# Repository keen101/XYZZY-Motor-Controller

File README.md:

# XYZZY-Motor-Controller
Open Source Hardware XYZZY Motor Controller Prototype
By Andrew Barney
Loveland, Colorado, USA
Nov-24-17

umm.. So this is a github of the XYZZY Open Source Motor Controller. It is currently not completley functional or ironed out. 80% complete. Needs some TLC.

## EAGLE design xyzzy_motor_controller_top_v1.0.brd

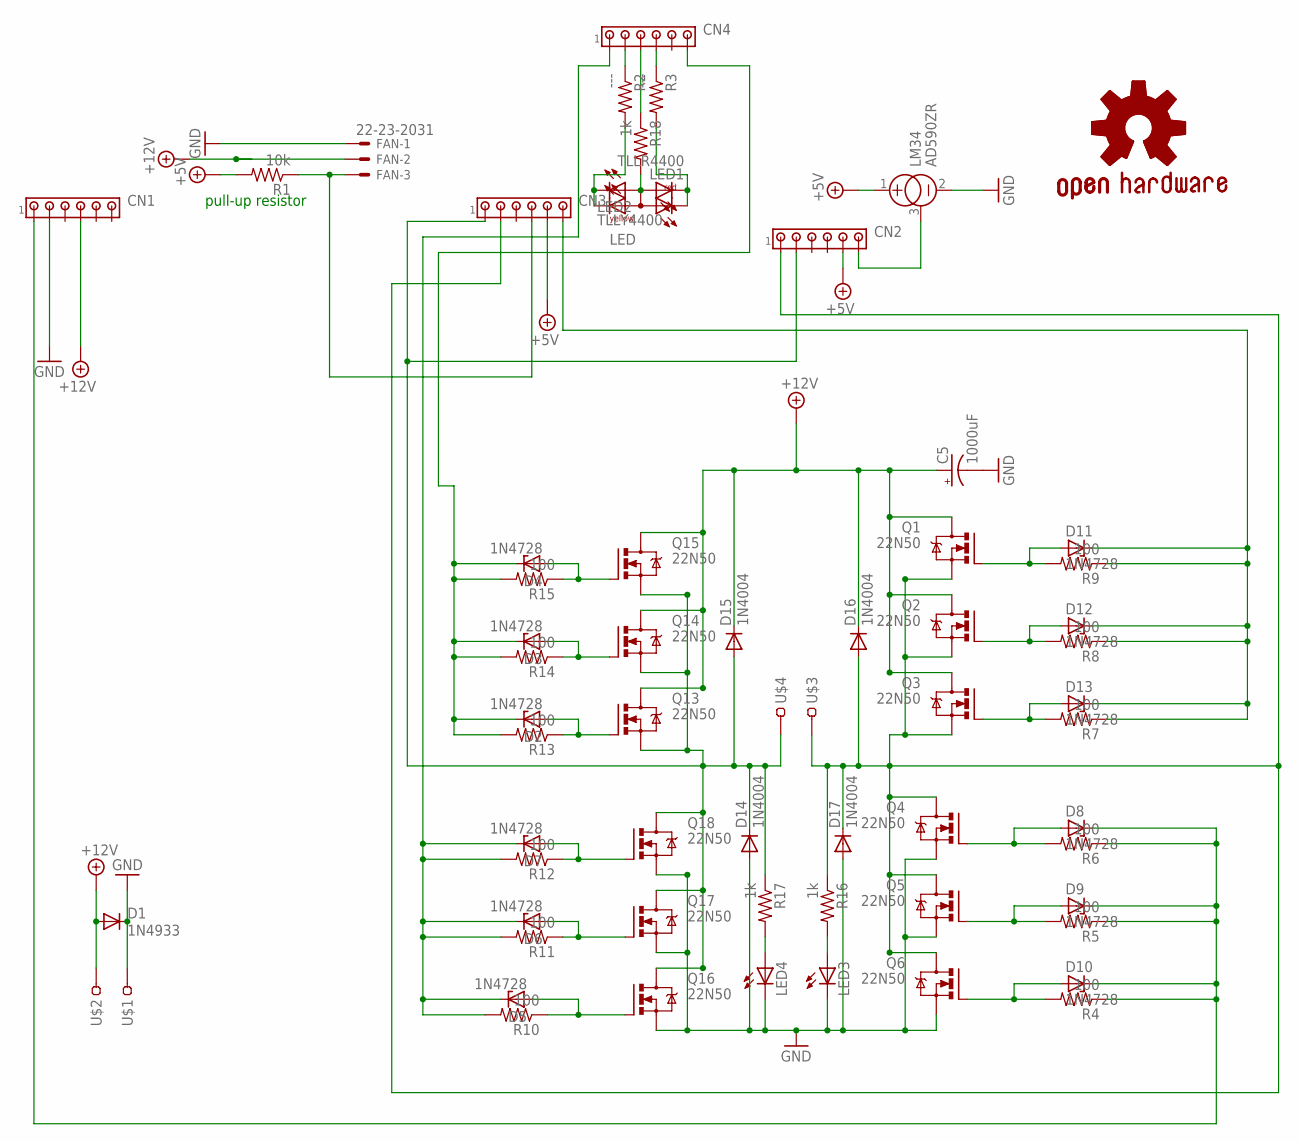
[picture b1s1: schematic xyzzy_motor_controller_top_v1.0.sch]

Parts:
C5: 1000uF; E5-13
CN1, CN2, CN3, CN4: MTA06-100; 10X06MTA
D1: 1N4933; DO41-10
D2, D3, D4, D5, D6, D7, D8, D9, D10, D11, D12, D13: 1N4728; DO41Z10
D14, D15, D16, D17: 1N4004; DO41-10
FAN: 22-23-2031
GOLD_ORB_SM2: OSHWLOGO_GOLD_ORB_MED; OSHW1
LED: DUOLED-RY-A; DUOLED-A-5MM
LED1: TLLR4400; LED3MM
LED2: TLLY4400; LED3MM
LED3, LED4: LED3MM
LM34: AD590ZR; TO92
Q1, Q2, Q3, Q4, Q5, Q6, Q13, Q14, Q15, Q16, Q17, Q18: 22N50; TO220BV
R1: 10k; 0207/12
R2, R3: ---; 0207/12
R4, R5, R6, R7, R8, R9, R10, R11, R12, R13, R14, R15: 100; 0207/12
R16, R17, R18: 1k; 0207/12
U$1, U$2, U$3, U$4: TAB-CON; SPADE

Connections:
+5V: CN2.5, CN3.5, LM34.1 (+), R1.2
+12V: C5.+, CN1.4, D1.A, D15.C, D16.C, FAN.2, Q1.D, Q2.D, Q3.D, Q13.D, Q14.D, Q15.D, U$2.P$1, U$2.P$2
GND: C5.-, CN1.2, D1.C, D14.A, D17.A, FAN.1, LED3.K (C), LED4.K (C), LM34.2 (-), Q4.S, Q5.S, Q6.S, Q16.S, Q17.S, Q18.S, U$1.P$1, U$1.P$2
unnamed: CN3.4, FAN.3, R1.1
unnamed: CN2.6, LM34.3 (CAN)
unnamed: CN2.2, CN3.1, D14.C, D15.A, Q13.S, Q14.S, Q15.S, Q16.D, Q17.D, Q18.D, R17.1, U$4.P$1, U$4.P$2
unnamed: D8.A, Q4.G, R6.2
unnamed: LED.CX (CY), LED2.K (C), R2.2
unnamed: CN4.2, R2.1
unnamed: CN4.1, D5.C, D6.C, D7.C, R10.2, R11.2, R12.2
unnamed: CN3.6, D11.C, D12.C, D13.C, R7.1, R8.1, R9.1
unnamed: CN4.4, R3.1
unnamed: LED.CR, LED1.K (C), R3.2
unnamed: LED3.A, R16.2
unnamed: D10.A, Q6.G, R4.2
unnamed: D9.A, Q5.G, R5.2
unnamed: D7.A, Q18.G, R12.1
unnamed: CN4.6, D2.C, D3.C, D4.C, R13.2, R14.2, R15.2
unnamed: CN1.1, D8.C, D9.C, D10.C, R4.1, R5.1, R6.1
unnamed: LED4.A, R17.2
unnamed: D6.A, Q17.G, R11.1
unnamed: CN2.1, CN3.2, D16.A, D17.C, Q1.S, Q2.S, Q3.S, Q4.D, Q5.D, Q6.D, R16.1, U$3.P$1, U$3.P$2
unnamed: D5.A, Q16.G, R10.1
unnamed: CN4.3, R18.1
unnamed: LED.A, LED1.A, LED2.A, R18.2
unnamed: D12.A, Q2.G, R8.2
unnamed: D11.A, Q1.G, R9.2
unnamed: D13.A, Q3.G, R7.2
unnamed: D3.A, Q14.G, R14.1
unnamed: D4.A, Q15.G, R15.1
unnamed: D2.A, Q13.G, R13.1

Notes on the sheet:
pull-up resistor

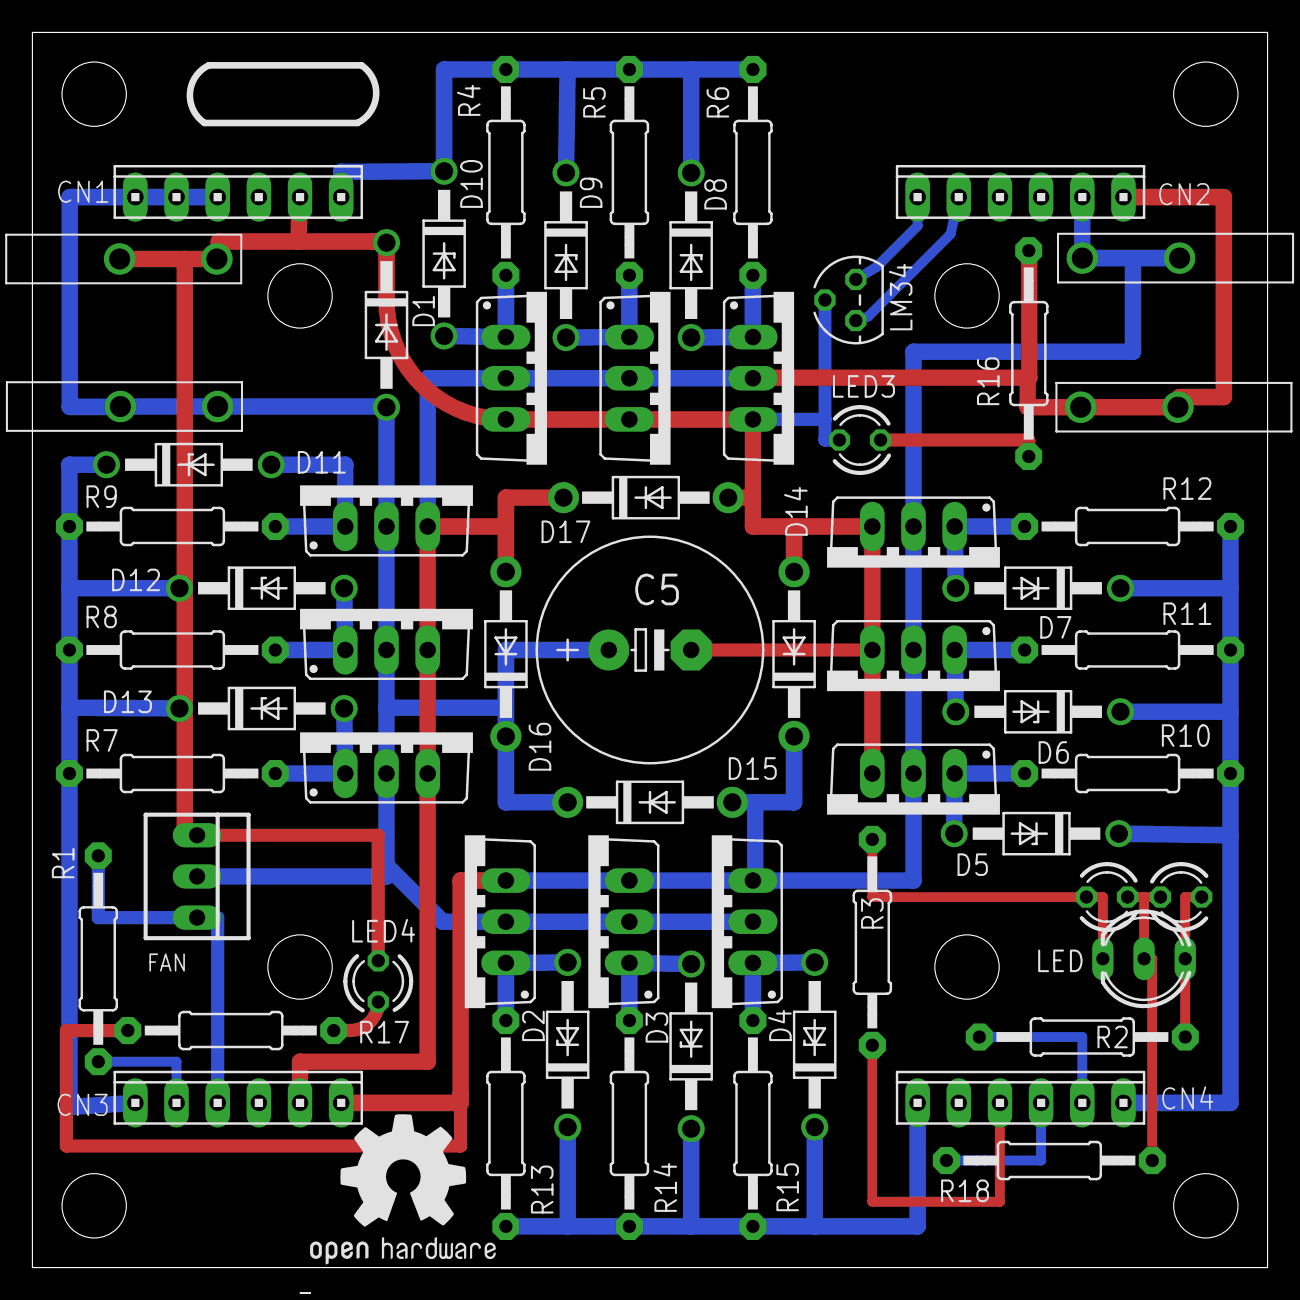
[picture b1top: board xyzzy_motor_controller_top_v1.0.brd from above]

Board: 2 copper layers, 76.2 x 76.2 mm, 64 parts (0 on the bottom side), 31 nets.

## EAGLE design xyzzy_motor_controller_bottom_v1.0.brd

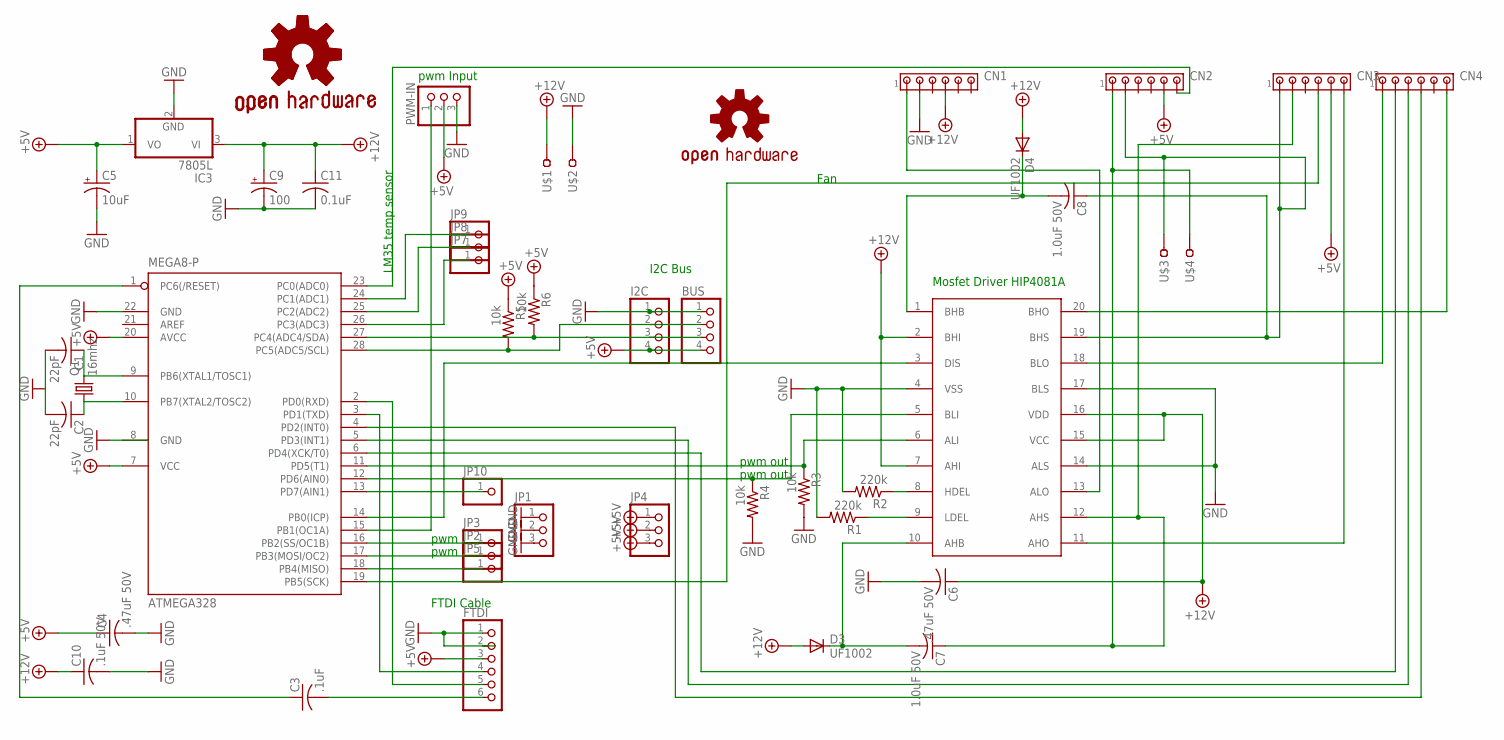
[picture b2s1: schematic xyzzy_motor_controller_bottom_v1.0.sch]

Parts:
ATMEGA328: MEGA8-P; DIL28-3
BUS: PINHD-1X4; 1X04
C1, C2: 22pF; C025_050-025X075
C3: .1uF; C050-025X075
C4, C6: .47uF 50V; C050-025X075
C5: 10uF; TT2D4L
C7: 1.0uF 50V; C025-025X050
C8: 1.0uF 50V; C050-025X075
C9: 100; TT2D4L
C10: .1uF 50V; C050-025X075
C11: 0.1uF; C050-025X075
CN1, CN2, CN3, CN4: MTA06-100; 10X06MTA
D3, D4: UF1002; DO41-10
FTDI: PINHD-1X6; 1X06
GOLD_ORB_SM1: OSHWLOGO_GOLD_ORB_LG; OSHW0
HIP4081A: HIP4081A; DIL20
I2C: PINHD-1X4; 1X04
IC3: 7805L; TO92
JP1, JP4: PINHD-1X3; 1X03
JP2, JP3, JP5, JP7, JP8, JP9, JP10: PINHD-1X1; 1X01
LOGO1: OSHW-LOGOL; OSHW-LOGO-L
PWM-IN: PINHD-1X3; 1X03
Q1: 16mhz; HC49U-V
R1, R2: 220k; 0207/12
R3, R4, R5, R6: 10k; 0207/12
U$1, U$2, U$3, U$4: TAB-CON; SPADE

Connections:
+5V: ATMEGA328.7 (VCC), ATMEGA328.20 (AVCC), BUS.4, C4.1, C5.+, CN2.5, CN3.5, I2C.4, IC3.1 (VO), JP4.1, JP4.2, JP4.3, PWM-IN.2, R5.1, R6.1
+12V: C6.1, C9.+, C10.1, C11.1, CN1.4, D3.A, D4.A, HIP4081A.2 (BHI), HIP4081A.7 (AHI), HIP4081A.15 (VCC), HIP4081A.16 (VDD), IC3.3 (VI), U$1.P$1, U$1.P$2
GND: ATMEGA328.8 (GND), ATMEGA328.22 (GND), BUS.1, C4.2, C5.-, C6.2, C9.-, C10.2, C11.2, CN1.2, FTDI.1, FTDI.2, HIP4081A.4 (VSS), HIP4081A.14 (ALS), HIP4081A.17 (BLS), I2C.1, IC3.2 (GND), JP1.1, JP1.2, JP1.3, PWM-IN.3, R1.2, R2.2, R3.2, R4.2, U$2.P$1, U$2.P$2
unnamed: ATMEGA328.17 (PB3(MOSI/OC2)), JP2.1
unnamed: C7.2, D3.C, HIP4081A.10 (AHB)
unnamed: ATMEGA328.4 (PD2(INT0)), CN4.4
unnamed: ATMEGA328.16 (PB2(SS/OC1B)), JP3.1
unnamed: ATMEGA328.9 (PB6(XTAL1/TOSC1)), C1.1, Q1.2
unnamed: ATMEGA328.2 (PD0(RXD)), FTDI.5
unnamed: ATMEGA328.11 (PD5(T1)), HIP4081A.6 (ALI), R3.1
unnamed: CN4.1, HIP4081A.18 (BLO)
unnamed: CN3.6, HIP4081A.11 (AHO)
unnamed: ATMEGA328.15 (PB1(OC1A)), PWM-IN.1
unnamed: ATMEGA328.6 (PD4(XCK/T0)), CN4.2
unnamed: ATMEGA328.10 (PB7(XTAL2/TOSC2)), C2.1, Q1.1
unnamed: C1.2, C2.2
unnamed: CN1.1, HIP4081A.13 (ALO)
unnamed: ATMEGA328.3 (PD1(TXD)), FTDI.4
unnamed: CN4.6, HIP4081A.20 (BHO)
unnamed: C8.2, D4.C, HIP4081A.1 (BHB)
unnamed: ATMEGA328.23 (PC0(ADC0)), CN2.6
unnamed: C7.1, CN2.1, CN3.2, HIP4081A.12 (AHS), U$4.P$1, U$4.P$2
unnamed: ATMEGA328.28 (PC5(ADC5/SCL)), BUS.2, I2C.2, R5.2
unnamed: ATMEGA328.12 (PD6(AIN0)), HIP4081A.5 (BLI), R4.1
unnamed: HIP4081A.9 (LDEL), R1.1
unnamed: HIP4081A.8 (HDEL), R2.1
unnamed: C8.1, CN2.2, CN3.1, HIP4081A.19 (BHS), U$3.P$1, U$3.P$2
unnamed: ATMEGA328.14 (PB0(ICP)), HIP4081A.3 (DIS)
unnamed: ATMEGA328.18 (PB4(MISO)), JP5.1
unnamed: ATMEGA328.19 (PB5(SCK)), CN3.4
unnamed: ATMEGA328.5 (PD3(INT1)), CN4.3
unnamed: C3.2, FTDI.6
unnamed: ATMEGA328.1 (PC6(/RESET)), C3.1
unnamed: ATMEGA328.27 (PC4(ADC4/SDA)), BUS.3, I2C.3, R6.2
unnamed: ATMEGA328.13 (PD7(AIN1)), JP10.1
unnamed: ATMEGA328.26 (PC3(ADC3)), JP7.1
unnamed: ATMEGA328.25 (PC2(ADC2)), JP8.1
unnamed: ATMEGA328.24 (PC1(ADC1)), JP9.1

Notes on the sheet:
Mosfet Driver HIP4081A
I2C Bus
Fan
LM35 temp sensor
pwm Input
pwm
pwm out
FTDI Cable

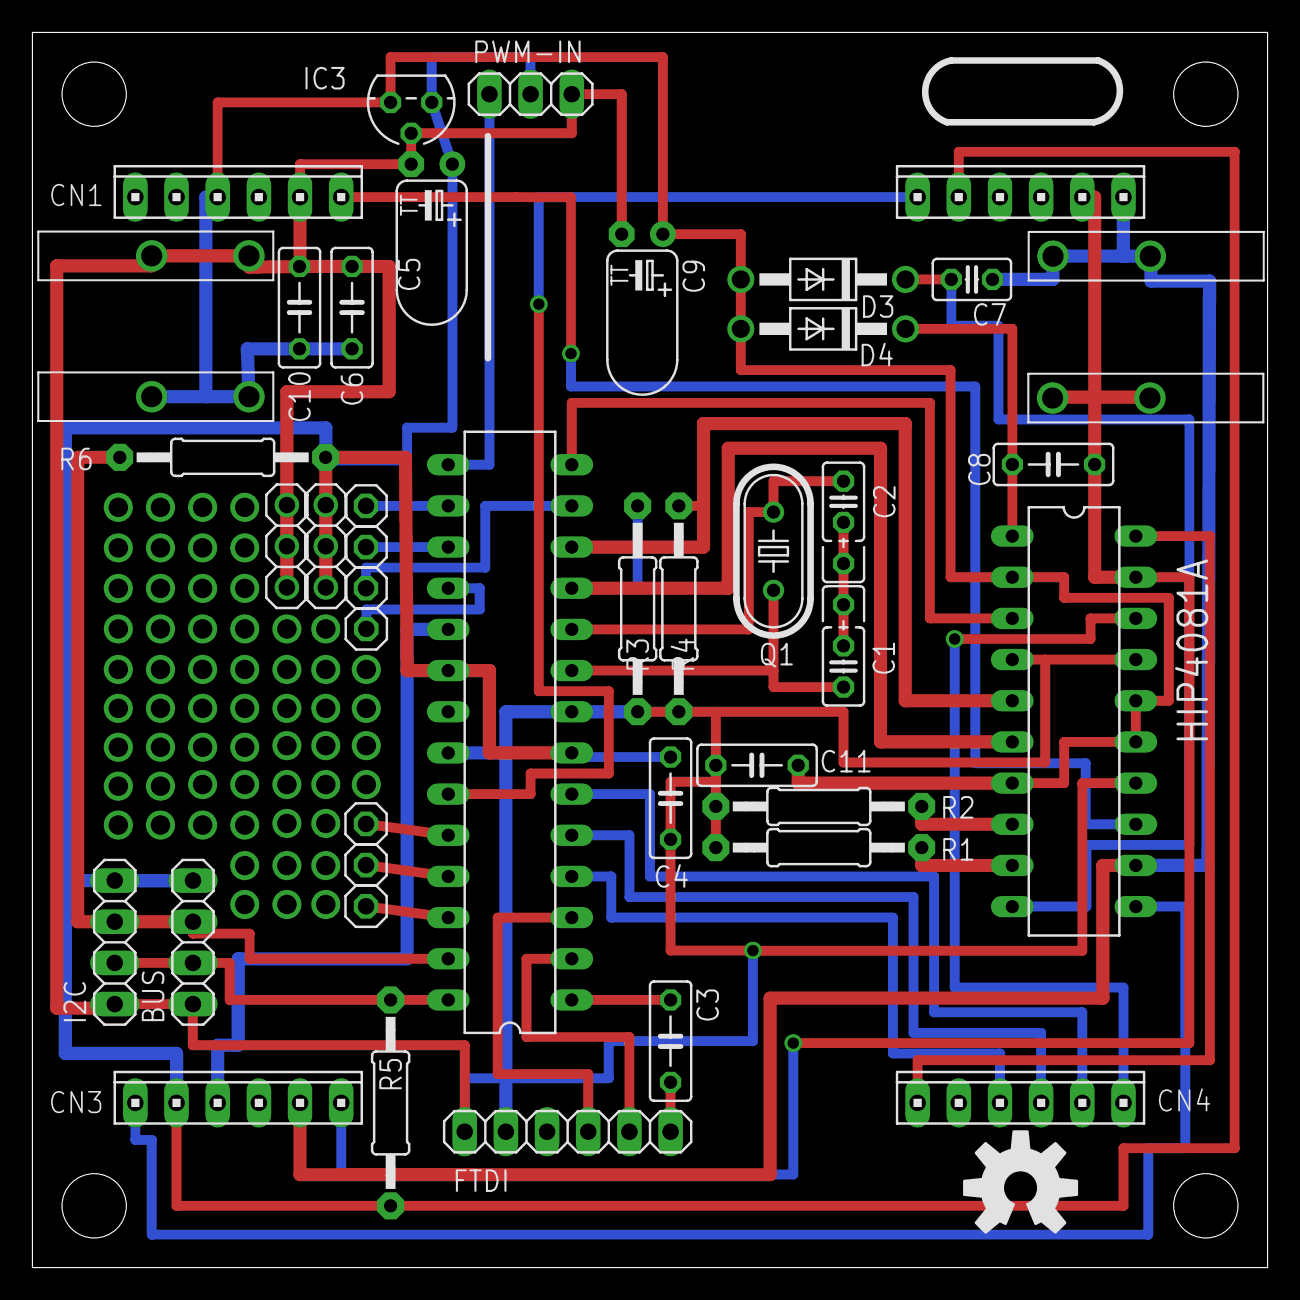
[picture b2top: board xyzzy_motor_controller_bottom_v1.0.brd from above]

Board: 2 copper layers, 76.2 x 76.2 mm, 46 parts (1 on the bottom side), 38 nets.

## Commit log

2017-11-20 first xyzzy commit
2017-11-20 added crappy arduino code
2017-11-21 added 3d printable test base to prevent shorting out/mounting
2017-11-24 OSMC and HIP4081A datasheet

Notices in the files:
parts and their libraries:
SparkFun-Aesthetics: Licensing: Creative Commons ShareAlike 4.0 International - https://creativecommons.org/licenses/by-sa/4.0
